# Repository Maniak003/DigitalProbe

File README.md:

<!DOCTYPE html>
<html lang="en" data-color-mode="auto" data-light-theme="light" data-dark-theme="dark">
  <head>
    <meta charset="utf-8">
  </head>
    <body class="logged-in env-production page-responsive page-blob" style="word-wrap: break-word;">
      <p> MSO5000 Digital probe. </p>

    </body>
</html>

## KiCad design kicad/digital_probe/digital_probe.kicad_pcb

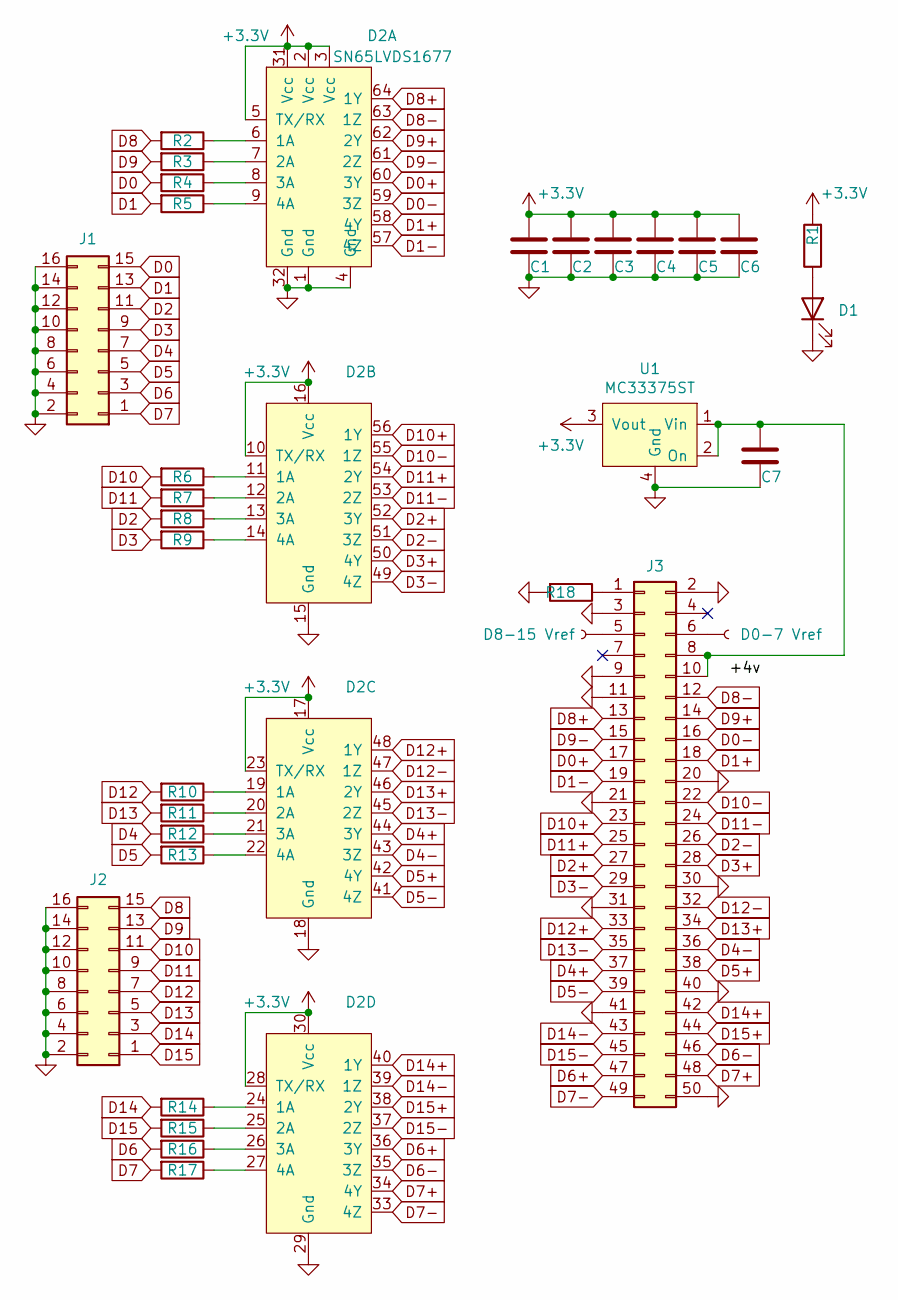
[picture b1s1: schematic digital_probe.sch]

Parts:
C1, C2, C3, C4, C5, C6, C7: 0.1; C_0402_1005Metric
D1: LED; LED_0603_1608Metric
D2: SN65LVDS1677; TSSOP-64_6.1x17mm_P0.5mm
J1, J2: Conn_02x08_Odd_Even; IDC-Header_2x08_P2.54mm_Horizontal
J3: Conn_02x25_Odd_Even; IDC-Header_2x25_P2.54mm_Horizontal
J4: D8-15 Vref; SMD-CONN
J5: D0-7 Vref; SMD-CONN
R1: 470; R_0402_1005Metric
R2, R3, R4, R5, R6, R7, R8, R9, R10, R11, R12, R13, R14, R15, R16, R17, R18: 100; R_0402_1005Metric
U1: MC33375ST; SOT-223

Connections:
+3V3: C1.1, C2.1, C3.1, C4.1, C5.1, C6.1, D2.2 (Vcc), D2.3 (Vcc), D2.5 (TX/RX), D2.10 (TX/RX), D2.16 (Vcc), D2.17 (Vcc), D2.23 (TX/RX), D2.28 (TX/RX), D2.30 (Vcc), D2.31 (Vcc), R1.2, U1.3 (Vout)
D0: J1.15, R4.2
D0+: D2.60 (3Y), J3.17
D0-: D2.59 (3Z), J3.16
D1: J1.13, R5.2
D1+: D2.58 (4Y), J3.18
D1-: D2.57 (4Z), J3.19
D2: J1.11, R8.2
D2+: D2.52 (3Y), J3.27
D2-: D2.51 (3Z), J3.26
D3: J1.9, R9.2
D3+: D2.50 (4Y), J3.28
D3-: D2.49 (4Z), J3.29
D4: J1.7, R12.2
D4+: D2.44 (3Y), J3.37
D4-: D2.43 (3Z), J3.36
D5: J1.5, R13.2
D5+: D2.42 (4Y), J3.38
D5-: D2.41 (4Z), J3.39
D6: J1.3, R16.2
D6+: D2.36 (3Y), J3.47
D6-: D2.35 (3Z), J3.46
D7: J1.1, R17.2
D7+: D2.34 (4Y), J3.48
D7-: D2.33 (4Z), J3.49
D8: J2.15, R2.2
D8+: D2.64 (1Y), J3.13
D8-: D2.63 (1Z), J3.12
D9: J2.13, R3.2
D9+: D2.62 (2Y), J3.14
D9-: D2.61 (2Z), J3.15
D10: J2.11, R6.2
D10+: D2.56 (1Y), J3.23
D10-: D2.55 (1Z), J3.22
D11: J2.9, R7.2
D11+: D2.54 (2Y), J3.25
D11-: D2.53 (2Z), J3.24
D12: J2.7, R10.2
D12+: D2.48 (1Y), J3.33
D12-: D2.47 (1Z), J3.32
D13: J2.5, R11.2
D13+: D2.46 (2Y), J3.34
D13-: D2.45 (2Z), J3.35
D14: J2.3, R14.2
D14+: D2.40 (1Y), J3.42
D14-: D2.39 (1Z), J3.43
D15: J2.1, R15.2
D15+: D2.38 (2Y), J3.44
D15-: D2.37 (2Z), J3.45
GND: C1.2, C2.2, C3.2, C4.2, C5.2, C6.2, C7.2, D1.1 (K), D2.1 (Gnd), D2.4 (Gnd), D2.15 (Gnd), D2.18 (Gnd), D2.29 (Gnd), D2.32 (Gnd), J1.2, J1.4, J1.6, J1.8, J1.10, J1.12, J1.14, J1.16, J2.2, J2.4, J2.6, J2.8, J2.10, J2.12, J2.14, J2.16, J3.2, J3.3, J3.9, J3.11, J3.20, J3.21, J3.30, J3.31, J3.40, J3.41, J3.50, R18.2, U1.4 (Gnd)
unnamed: C7.1, J3.8, J3.10, U1.1 (Vin), U1.2 (On)
unnamed: D1.2 (A), R1.1
unnamed: D2.6 (1A), R2.1
unnamed: D2.7 (2A), R3.1
unnamed: D2.8 (3A), R4.1
unnamed: D2.9 (4A), R5.1
unnamed: D2.11 (1A), R6.1
unnamed: D2.12 (2A), R7.1
unnamed: D2.13 (3A), R8.1
unnamed: D2.14 (4A), R9.1
unnamed: D2.19 (1A), R10.1
unnamed: D2.20 (2A), R11.1
unnamed: D2.21 (3A), R12.1
unnamed: D2.22 (4A), R13.1
unnamed: D2.24 (1A), R14.1
unnamed: D2.25 (2A), R15.1
unnamed: D2.26 (3A), R16.1
unnamed: D2.27 (4A), R17.1
unnamed: J3.1, R18.1
unnamed: J3.5, J4.1
unnamed: J3.6, J5.1

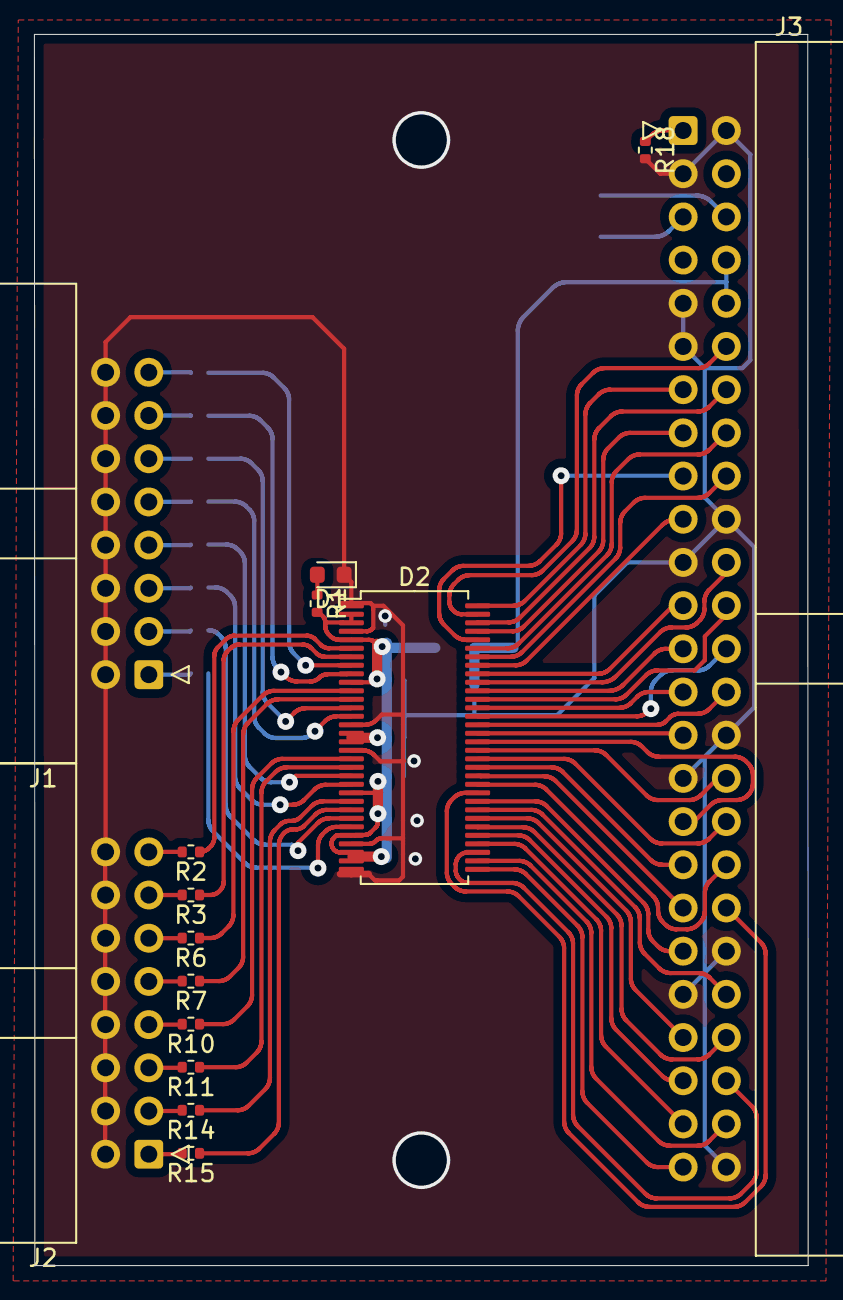
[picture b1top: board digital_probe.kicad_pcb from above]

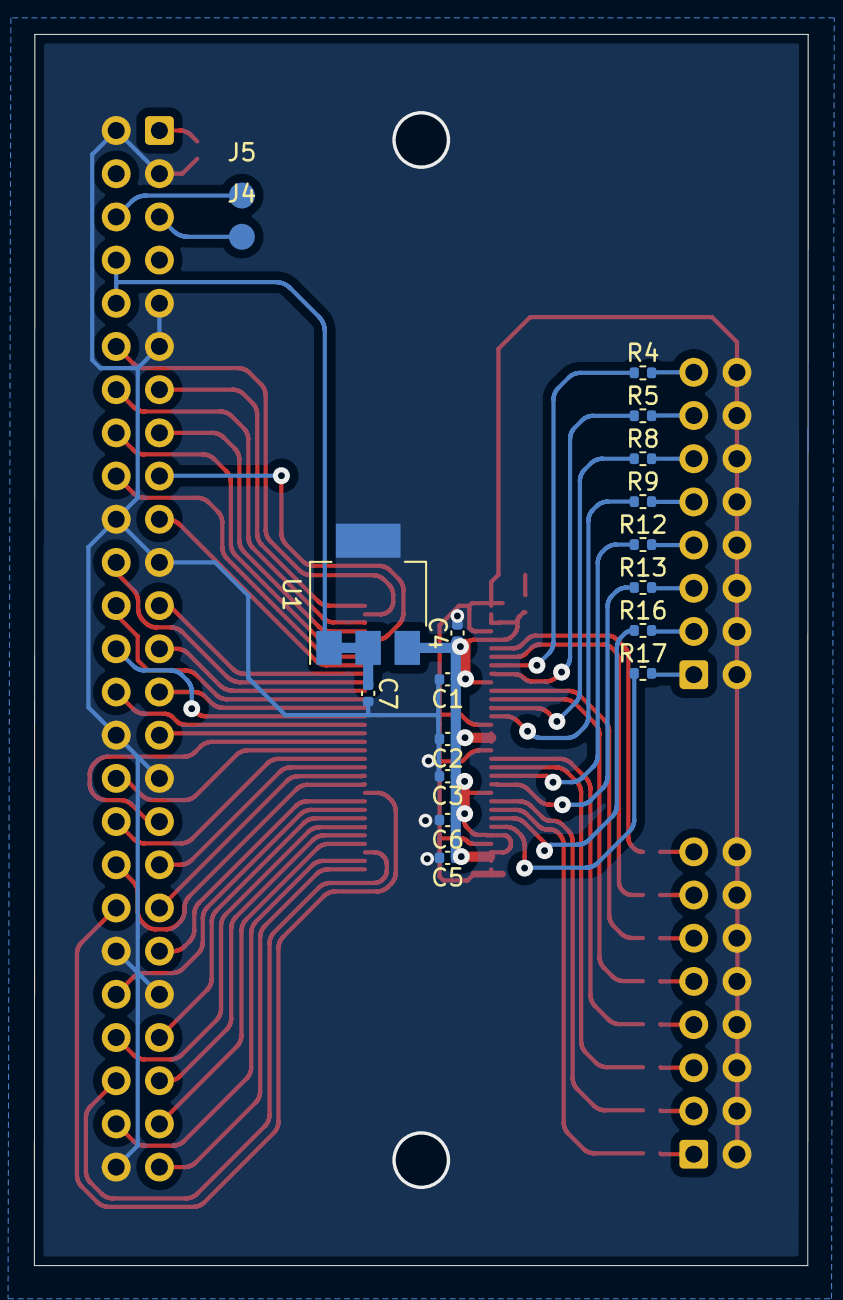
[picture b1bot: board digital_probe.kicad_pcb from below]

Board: 2 copper layers, 45.5 x 72.4 mm, 33 parts (18 on the bottom side), 71 nets.

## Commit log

2022-06-01 MSO5000
2022-06-01 изменено: README.md
2022-06-01 новый файл: kicad/digital_probe/digital_probe-cache.lib новый файл: kicad/digital_probe/digital_probe.kicad_pcb новый файл: kicad/digital_probe/digital_probe.kicad_pcb-bak новый файл: kicad/digital_p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
2022-08-21 изменено: kicad/digital_probe/digital_probe-cache.lib изменено: kicad/digital_probe/digital_probe.kicad_pcb изменено: kicad/digital_probe/digital_probe.kicad_pcb-bak изменено: kicad/digital_probe/dig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
2022-08-22 новый файл: Documents/IMG_20220822_103320.jpg новый файл: Documents/MC33375-D.PDF новый файл: Documents/SN65LVDM1677DGG.pdf изменено: kicad/digital_probe/digital_probe.pro
2022-08-22 новый файл: Documents/IMG_20220822_155239.jpg новый файл: Documents/IMG_20220822_165848.jpg новый файл: FreeCAD/box.FCStd новый файл: FreeCAD/box.stl новый файл: FreeCAD/cover.FCStd новый файл: FreeC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
2022-08-22 изменено: FreeCAD/box.FCStd изменено: FreeCAD/cover.FCStd изменено: FreeCAD/cover.stl
2022-08-31 изменено: kicad/digital_probe/digital_probe.kicad_pcb изменено: kicad/digital_probe/digital_probe.kicad_pcb-bak новый файл: kicad/digital_probe/gerber/digital_probe.zip
2022-10-20 новый файл: Documents/IMG_20221001_132513.jpg изменено: kicad/digital_probe/digital_probe-cache.lib изменено: kicad/digital_probe/digital_probe.kicad_pcb изменено: kicad/digital_probe/digital_probe.k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
2022-10-20 изменено: kicad/digital_probe/gerber/digital_probe.zip
